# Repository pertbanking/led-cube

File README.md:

# led-cube
This is the repository for the code, schematics, and boards of an 8x8x8 LED cube.

## Folder hierarchy

Folder / File            | Purpose                                                          
------------------------- | ----------------------------------------------------------------
`arduino_serial_client/`  | Arduino code.
`pcb/`                    | Contains PCB schematics and boards for the multiplexing circuit. 
&nbsp;&nbsp;&nbsp;&nbsp;`/master pcb/`        | The decoder selector circuit
&nbsp;&nbsp;&nbsp;&nbsp;`/slave pcb/`         | The D Flip-Flop circuit for each row of LEDs
&nbsp;&nbsp;&nbsp;&nbsp;`/datasheets/`        | Datasheets for the ICs in the circuit
`pi/`                     | Contains all animation code. Build the project in this directory with its `CMakeLists.txt` file (see below). So named because I recommend you run this on a Raspberry Pi.
&nbsp;&nbsp;&nbsp;&nbsp;`/serial/`            | The standalone `serial` library (see below).
&nbsp;&nbsp;&nbsp;&nbsp;`/src/`               | Code source.
&nbsp;&nbsp;&nbsp;&nbsp;&nbsp;&nbsp;&nbsp;&nbsp;`/LEDCube.h`     | Represents the cube. Sends data to the Arduino through `serial`. Contains many helpful drawing functions. 
&nbsp;&nbsp;&nbsp;&nbsp;&nbsp;&nbsp;&nbsp;&nbsp;`/Animation.h`   | Header file for the generic animation. Extend this class to make your own animation!
&nbsp;&nbsp;&nbsp;&nbsp;&nbsp;&nbsp;&nbsp;&nbsp;`/animations/`   | Contains animation files. Each file represents a different animation.
&nbsp;&nbsp;&nbsp;&nbsp;&nbsp;&nbsp;&nbsp;&nbsp;`/main.cpp`      | An example client program. It is highly recommended you specialize this program instead of making your own.

More details coming soon.

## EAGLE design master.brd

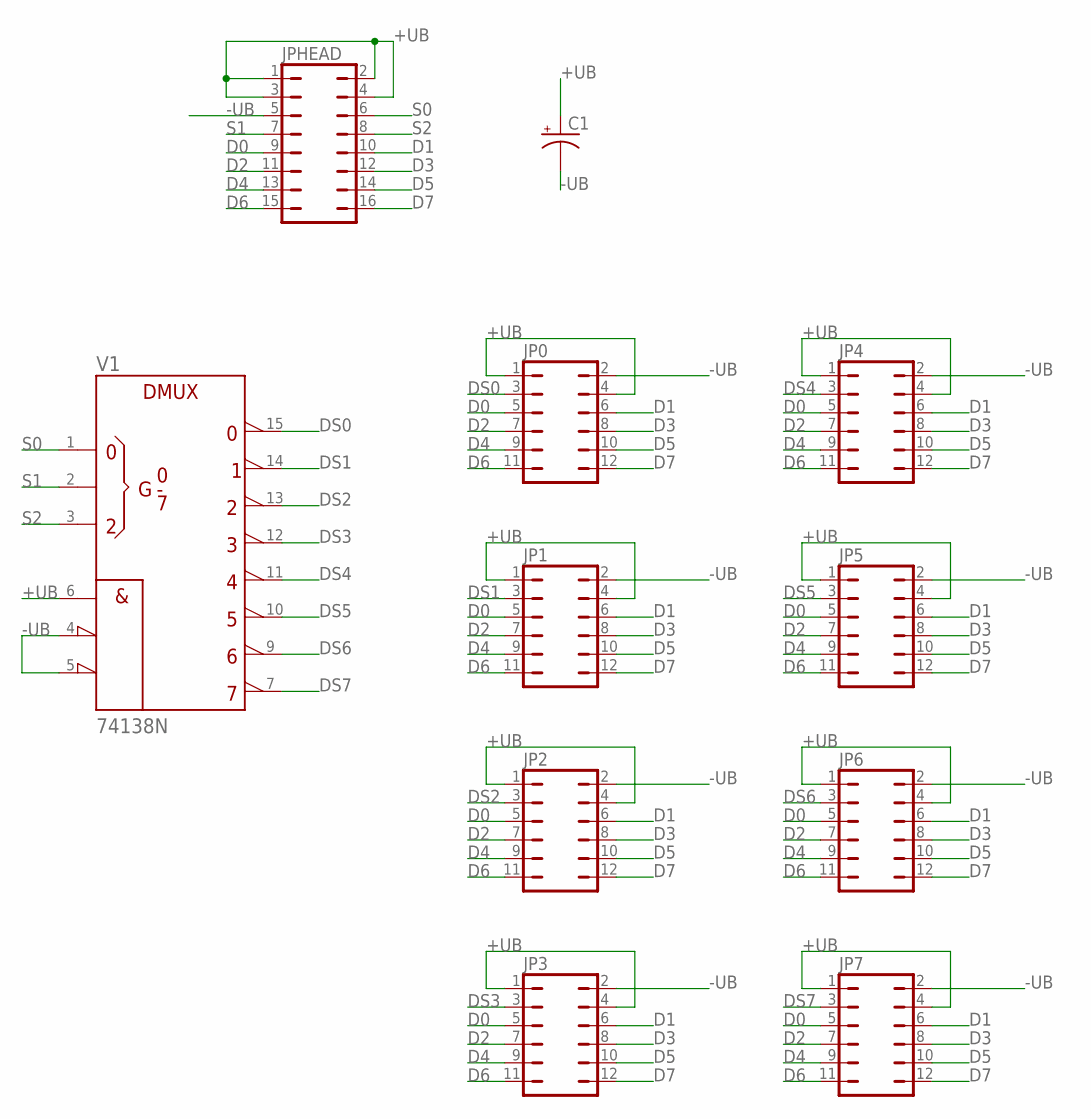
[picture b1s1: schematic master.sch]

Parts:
C1: CPOL-USTT2D4; TT2D4
JP0, JP1, JP2, JP3, JP4, JP5, JP6, JP7: JP6Q
JPHEAD: JP8Q
V1: 74138N; DIL16

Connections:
+UB: C1.+, JP0.1, JP0.4, JP1.1, JP1.4, JP2.1, JP2.4, JP3.1, JP3.4, JP4.1, JP4.4, JP5.1, JP5.4, JP6.1, JP6.4, JP7.1, JP7.4, JPHEAD.1, JPHEAD.2, JPHEAD.3, JPHEAD.4, V1.6 (G1), V1.16 (+UB)
-UB: C1.-, JP0.2, JP1.2, JP2.2, JP3.2, JP4.2, JP5.2, JP6.2, JP7.2, JPHEAD.5, V1.4 (!G2A), V1.5 (!G2B), V1.8 (-UB)
D0: JP0.5, JP1.5, JP2.5, JP3.5, JP4.5, JP5.5, JP6.5, JP7.5, JPHEAD.9
D1: JP0.6, JP1.6, JP2.6, JP3.6, JP4.6, JP5.6, JP6.6, JP7.6, JPHEAD.10
D2: JP0.7, JP1.7, JP2.7, JP3.7, JP4.7, JP5.7, JP6.7, JP7.7, JPHEAD.11
D3: JP0.8, JP1.8, JP2.8, JP3.8, JP4.8, JP5.8, JP6.8, JP7.8, JPHEAD.12
D4: JP0.9, JP1.9, JP2.9, JP3.9, JP4.9, JP5.9, JP6.9, JP7.9, JPHEAD.13
D5: JP0.10, JP1.10, JP2.10, JP3.10, JP4.10, JP5.10, JP6.10, JP7.10, JPHEAD.14
D6: JP0.11, JP1.11, JP2.11, JP3.11, JP4.11, JP5.11, JP6.11, JP7.11, JPHEAD.15
D7: JP0.12, JP1.12, JP2.12, JP3.12, JP4.12, JP5.12, JP6.12, JP7.12, JPHEAD.16
DS0: JP0.3, V1.15 (Y0)
DS1: JP1.3, V1.14 (Y1)
DS2: JP2.3, V1.13 (Y2)
DS3: JP3.3, V1.12 (Y3)
DS4: JP4.3, V1.11 (Y4)
DS5: JP5.3, V1.10 (Y5)
DS6: JP6.3, V1.9 (Y6)
DS7: JP7.3, V1.7 (Y7)
S0: JPHEAD.6, V1.1 (A)
S1: JPHEAD.7, V1.2 (B)
S2: JPHEAD.8, V1.3 (C)

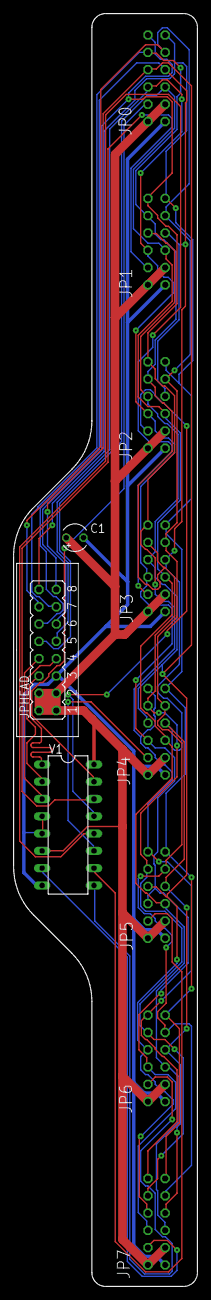
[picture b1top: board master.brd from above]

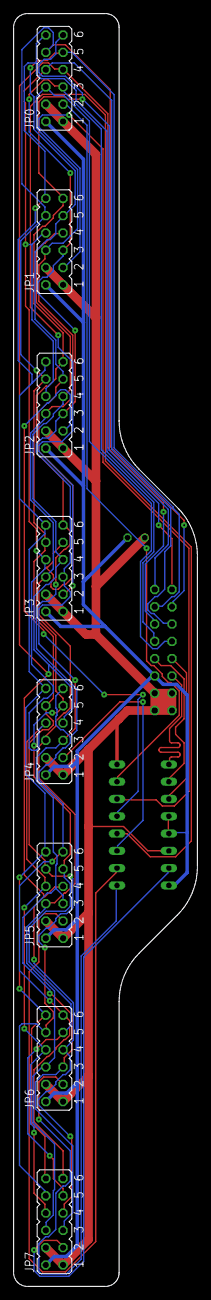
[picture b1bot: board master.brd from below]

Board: 2 copper layers, 27.0 x 187.0 mm, 11 parts (8 on the bottom side), 21 nets.

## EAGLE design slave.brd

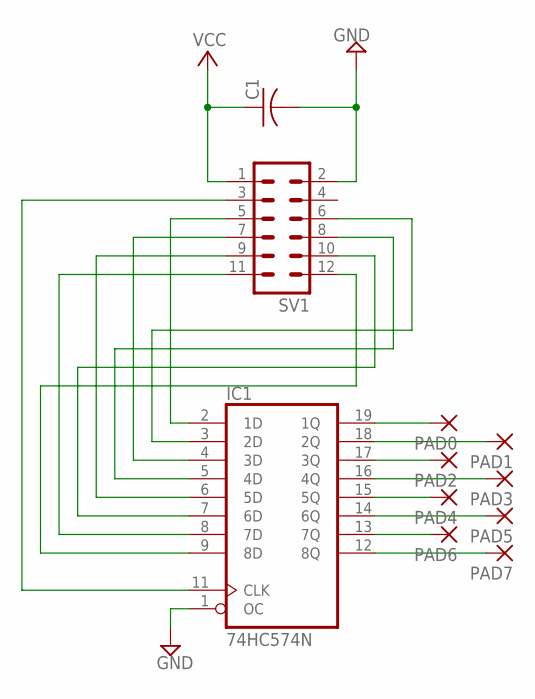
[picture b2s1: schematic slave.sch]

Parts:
C1: C-USC0805; C0805
IC1: 74HC574N; DIL20
PAD0, PAD1, PAD2, PAD3, PAD4, PAD5, PAD6, PAD7: 2,54/0,8
SV1: MA06-2

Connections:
CLK: IC1.11 (CLK), SV1.3
GND: C1.2, IC1.1 (OC), IC1.10 (GND), SV1.2
IN0: IC1.2 (1D), SV1.5
IN1: IC1.3 (2D), SV1.6
IN2: IC1.4 (3D), SV1.7
IN3: IC1.5 (4D), SV1.8
IN4: IC1.6 (5D), SV1.9
IN5: IC1.7 (6D), SV1.10
IN6: IC1.8 (7D), SV1.11
IN7: IC1.9 (8D), SV1.12
unnamed: IC1.19 (1Q), PAD0.1
unnamed: IC1.18 (2Q), PAD1.1
unnamed: IC1.17 (3Q), PAD2.1
unnamed: IC1.16 (4Q), PAD3.1
unnamed: IC1.15 (5Q), PAD4.1
unnamed: IC1.14 (6Q), PAD5.1
unnamed: IC1.13 (7Q), PAD6.1
unnamed: IC1.12 (8Q), PAD7.1
VCC: C1.1, IC1.20 (VCC), SV1.1

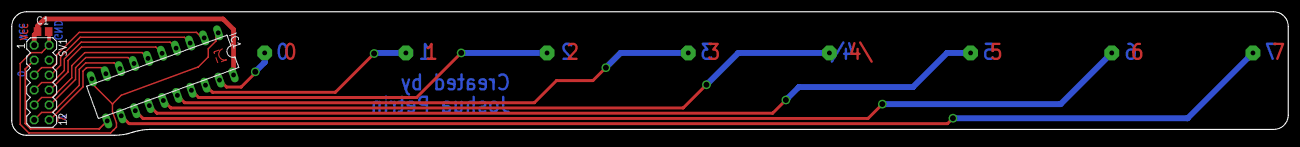
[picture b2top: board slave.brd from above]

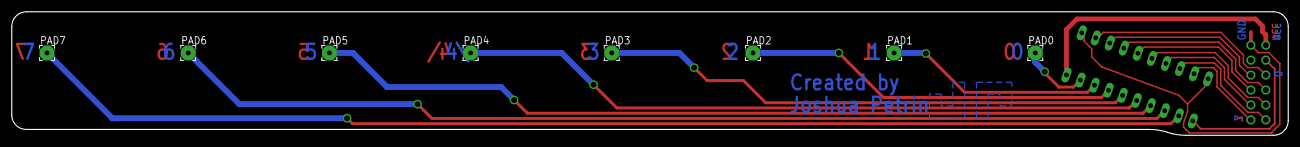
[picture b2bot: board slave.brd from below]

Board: 2 copper layers, 217.0 x 21.0 mm, 11 parts (8 on the bottom side), 19 nets.

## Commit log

2019-01-12 Created slave board schematic and layout
2019-01-12 Added IC datasheets
2019-01-12 changed mah logo
2019-06-15 final version prototype
2019-06-20 first animation working!
2019-06-21 started cube class, no debuging yet
2019-06-25 Compiles on Linux, not sure about any other platforms
2019-06-26 f you
2019-06-26 added the serial
2019-06-27 Added Rain.cpp
2019-06-30 mutex crap worked out, still a little work to do
2019-06-30 Added PlaneWop.cpp
2019-06-30 organized some stuff
2019-06-30 Updated Cmakelists.txt to include serial library
2019-06-30 cmake is ass
2019-07-01 finally got this effing thing working
2019-07-01 segfaulting somewhere
2019-07-03 minor fix
2019-07-03 fixed da bug
2019-07-03 added docs
2019-07-03 added a smart delay for animation calculation (see main.cpp)
2019-07-05 fixed mutex stuff
2019-07-08 Added Waves_I.cpp - sin*cos waveform generator
2019-07-09 line function + cubewop animation
2019-07-09 fixed wave boundary
2019-07-12 drawBox half implemented, CubeWop_I complete
2019-07-12 Added the flash/fade animation + cleaned up some stuff
2019-07-13 didn't like the name :/
2019-07-13 Added Waves II -- cos ripple
2019-07-22 small changes with warnings enabled
2019-07-22 created the an OpenGL program
2019-07-22 whitespace
2019-07-22 initialize the usb streamer class
2019-07-23 reference #3: LEDCube has been virtualized (i.e. it has no virtual methods but you can't make an instance of it anymore) + LEDCubeUSBStreamer class
2019-07-25 Animation 'CubeConstructor'
2019-07-25 merged with master, worked on LEDCubeVisualizer.cpp/.h
2019-07-26 references #1: Created LEDCubeVisualizer class, render thread is freezing, need to add condition variable?
2019-11-30 making the snake solver
2019-12-06 forced all frames to go to 0 on the reset() call
2019-12-23 adding SnakeSolver and a few changes to the main program
2019-12-23 i am angry that this isn't working >:(
